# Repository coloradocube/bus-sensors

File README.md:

# Satellite bus sensors

A separate board containing the sensors for the satellite bus. The sensors are telemetry data sources.

## Sensor information

### High-precision temperature sensor (external)

1. Part number: TMP117.
2. Form factor: Breakout.
3. Product page: https://www.sparkfun.com/products/15805
4. Vendor: SparkFun
5. SKU: SEN-15805
6. Board-level connector:
   1. Format: Surface-mount.
   2. Product page: https://www.sparkfun.com/products/14417
   3. Vendor: SparkFun
   4. SKU: PRT-14417
   5. 2D/3D models page: https://www.snapeda.com/parts/PRT-14417/SparkFun%20Electronics/view-part/
   6. KiCAD footprint: https://github.com/KiCad/Connectors_JST.pretty/blob/master/JST_SH_BM04B-SRSS-TB_04x1.00mm_Straight.kicad_mod
7. Operating voltage (typical): 1.8V-5.5V (3.3V).

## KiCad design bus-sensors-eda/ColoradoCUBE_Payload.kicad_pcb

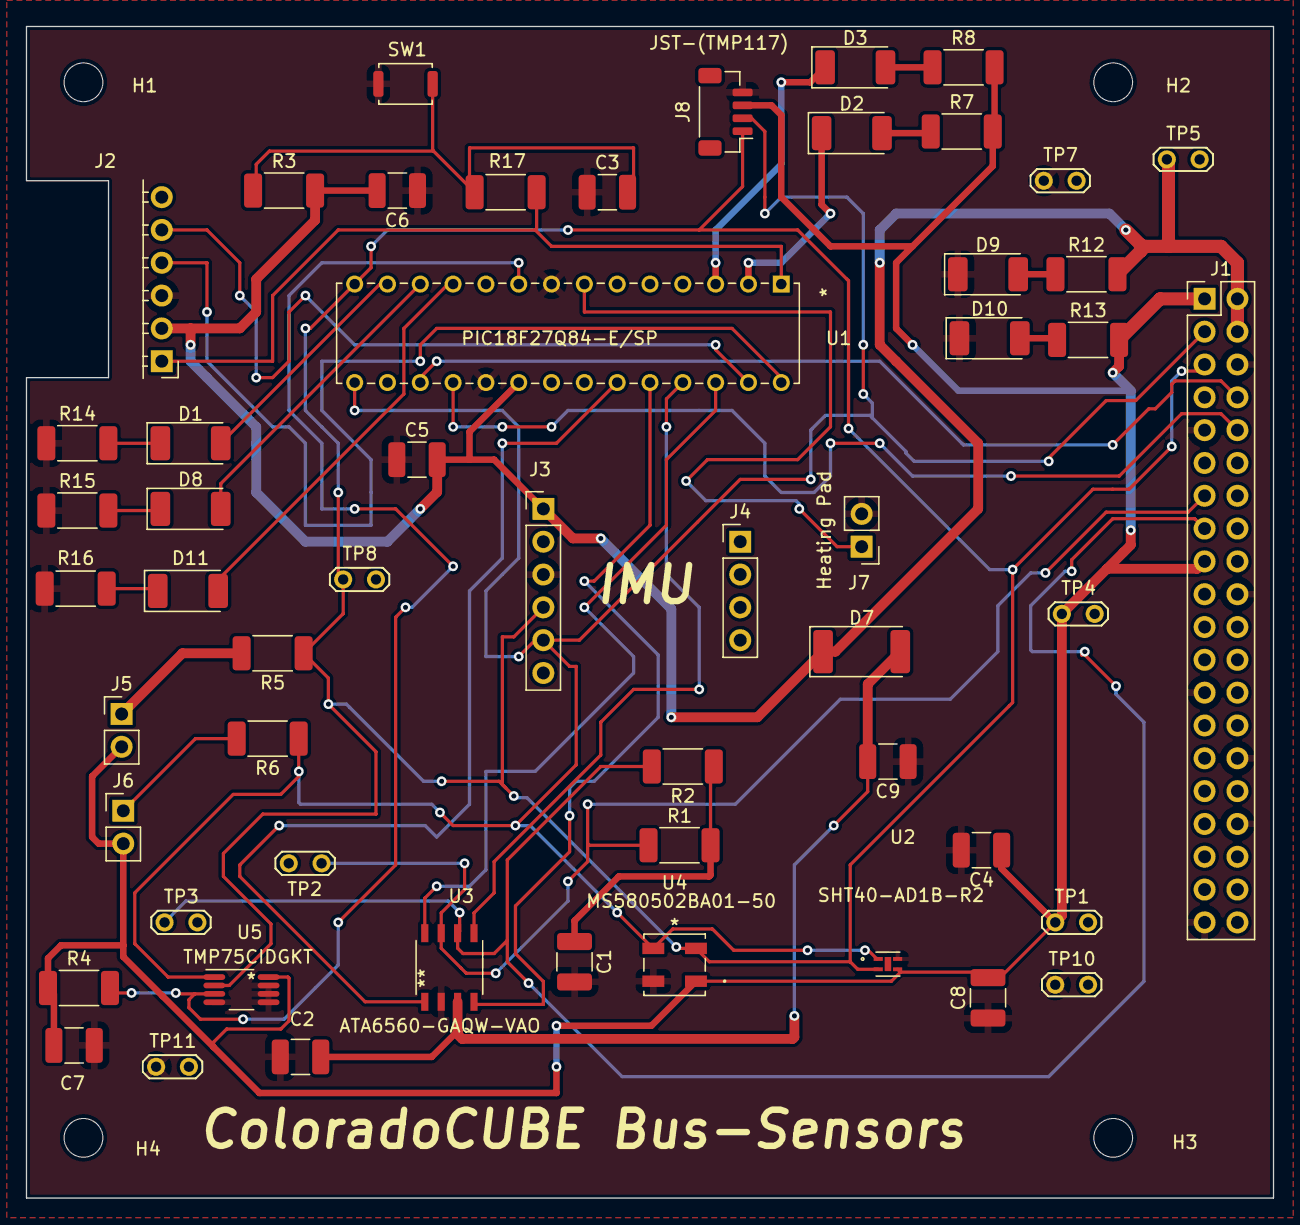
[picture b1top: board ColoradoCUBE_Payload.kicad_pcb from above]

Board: 2 copper layers, 96.5 x 90.7 mm, 58 parts (0 on the bottom side), 35 nets.

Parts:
C1: 4.7nF; C_1210_3225Metric_Pad1.33x2.70mm_HandSolder
C2: 100nF; C_1210_3225Metric_Pad1.33x2.70mm_HandSolder
C3, C4, C5, C6, C7, C8: 0.1uF; C_1210_3225Metric_Pad1.33x2.70mm_HandSolder
C9: 22uF; C_1210_3225Metric_Pad1.33x2.70mm_HandSolder
D1, D8, D11: LED_Filled; LED_2010_5025Metric_Pad1.52x2.65mm_HandSolder
D2, D9, D10: RED; LED_2010_5025Metric_Pad1.52x2.65mm_HandSolder
D3: GREEN; LED_2010_5025Metric_Pad1.52x2.65mm_HandSolder
D7: DIODE; D_2512_6332Metric_Pad1.52x3.35mm_HandSolder
H1, H2, H3, H4: 3mm_Mounting_Hole; MountingHole_3mm
J1: Conn_02x20_Odd_Even; PinHeader_2x20_P2.54mm_Vertical
J2: Conn_01x06; PinHeader_1x06_P2.54mm_Horizontal
J3: Conn_01x06; PinHeader_1x06_P2.54mm_Vertical
J4: Conn_01x04; PinHeader_1x04_P2.54mm_Vertical
J5, J6, J7: Conn_01x02; PinHeader_1x02_P2.54mm_Vertical
J8: Conn_01x04; JST_SH_BM04B-SRSS-TB_1x04-1MP_P1.00mm_Vertical
R1, R2: 60; R_2010_5025Metric_Pad1.40x2.65mm_HandSolder
R3, R4: 10K; R_2010_5025Metric_Pad1.40x2.65mm_HandSolder
R5, R6: 10k; R_2010_5025Metric_Pad1.40x2.65mm_HandSolder
R7, R8: 330; R_2010_5025Metric_Pad1.40x2.65mm_HandSolder
R12: 470; R_2010_5025Metric_Pad1.40x2.65mm_HandSolder
R13: 270; R_2010_5025Metric_Pad1.40x2.65mm_HandSolder
R14, R15, R16: 1k; R_2010_5025Metric_Pad1.40x2.65mm_HandSolder
R17: 100; R_2010_5025Metric_Pad1.40x2.65mm_HandSolder
SW1: SW_SPST; SW_Push_SPST_NO_Alps_SKRK
TP1, TP2, TP3, TP4, TP5, TP7, TP8, TP10, TP11: TestPoint; TestPoint_2Pads_Pitch2.54mm_Drill0.8mm
U1: PIC18F27Q84-E/SP; PIC18F27Q84-E&slash_SP
U2: SHT40-AD1B-R2
U3: ATA6560-GAQW-VAO
U4: MS580502BA01-50
U5: TMP75CIDGKT

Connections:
/+3V3_VDD: C4.1, C7.2, C8.2, J1.1, J1.17, J5.2, J6.2, J8.3, R4.1, R7.2, R8.2, R13.2, TP1.1, TP4.1, U2.3 (VDD), U4.1 (VDD), U5.8 (VS)
/+5V_VDD: C5.2, C6.2, D7.1 (A), J1.2, J1.4, J2.2, J3.1, R3.2, R12.2, TP5.1, U1.20 (VDD)
/ALERT_TEM: R4.2, U1.9 (RA7), U5.3 (ALERT)
/CAN_Transceiver/CANH: J1.13, R1.1, TP2.1, U3.7 (CANH)
/CAN_Transceiver/CANL: J1.15, R2.2, TP3.1, U3.6 (CANL)
/CAN_Transceiver/CAN_RX: U1.24 (RB3), U3.4 (RXD)
/CAN_Transceiver/CAN_TX: U1.23 (RB2), U3.1 (TXD)
/CAN_Transceiver/NSIL: U1.25 (RB4), U3.5 (NSIL)
/CAN_Transceiver/PWR: C2.1, C9.2, D7.2 (K), U3.3 (VCC)
/CAN_Transceiver/STBY: U1.26 (RB5), U3.8 (STBY)
/ICSPC: J2.5, U1.27 (RB6/ICSPCLK)
/ICSPD: J2.4, U1.28 (RB7/ICSPDAT)
/LED_1: D2.1 (K), U1.2 (RA0)
/LED_2: D3.1 (K), U1.3 (RA1)
/MCLR: J2.1, R17.2, U1.1 (*MCLR/VPP/RE3)
/RC0_D11: D11.2 (A), U1.11 (RC0)
/RC1_D12: D8.2 (A), U1.12 (RC1)
/RC2_D13: D1.2 (A), U1.13 (RC2)
/RC6_TX: J1.8, U1.17 (RC6)
/RC7_RX: J1.10, U1.18 (RC7)
/SCL_RC3: J1.5, J3.4, J8.1, R5.1, TP8.1, U1.14 (RC3), U2.2 (SCL), U4.2 (SCL), U5.2 (SCL)
/SDA_RC4: J1.3, J3.5, J8.2, R6.1, U1.15 (RC4), U2.1 (SDA), U4.3 (SDA), U5.1 (SDA)
GND: C1.2, C2.2, C3.1, C4.2, C5.1, C6.1, C7.1, C8.1, C9.1, D9.1 (K), D10.1 (K), J1.6, J1.9, J1.20, J1.25, J1.30, J1.34, J1.39, J2.3, J3.3, J7.2, J8.4, R14.2, R15.2, R16.2, SW1.1 (A), TP7.1, TP10.1, TP11.1, U1.8 (VSS), U1.19 (VSS), U2.4 (VSS), U3.2 (GND), U4.4 (GND), U5.4 (GND), U5.5 (A2), U5.6 (A1), U5.7 (A0)
unnamed: C1.1, R1.2, R2.1
unnamed: C3.2, R3.1, R17.1, SW1.2 (B)
unnamed: D1.1 (K), R14.1
unnamed: D2.2 (A), R7.1
unnamed: D3.2 (A), R8.1
unnamed: D8.1 (K), R15.1
unnamed: D9.2 (A), R12.1
unnamed: D10.2 (A), R13.1
unnamed: D11.1 (K), R16.1
unnamed: J5.1, R5.2
unnamed: J6.1, R6.2
unnamed: J7.1, U1.7 (RA5)

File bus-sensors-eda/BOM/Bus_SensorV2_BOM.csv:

Component Count:,54,,,,,,,,,,
,,,,,,,,,,,
Ref,Qnty,Value,Cmp name,Footprint,Description,JLCPCBPRT#,Digi-Key PRT#,SparkFun,Mouser PRT #,Purchase Link,
,,,,,,,,,,,
"C1, ",1,4.7nF,C,Capacitor_SMD:C_1210_3225Metric_Pad1.33x2.70mm_HandSolder,Unpolarized capacitor,,,,,,
,,,,,,,,,,,
"C2, ",1,100nF,C,Capacitor_SMD:C_1210_3225Metric_Pad1.33x2.70mm_HandSolder,Unpolarized capacitor,,,,,,
,,,,,,,,,,,
"C3, C4, C5, C6, C7, C8, ",6,0.1uF,C,Capacitor_SMD:C_1210_3225Metric_Pad1.33x2.70mm_HandSolder,Unpolarized capacitor,,,,,,
,,,,,,,,,,,
"C9, ",1,22uF,C,Capacitor_SMD:C_1210_3225Metric_Pad1.33x2.70mm_HandSolder,Unpolarized capacitor,,,,,,
,,,,,,,,,,,
"D1, D8, D11, ",3,LED_Filled,LED_Filled,LED_SMD:LED_2010_5025Metric_Pad1.52x2.65mm_HandSolder,"Light emitting diode, filled shape",,,,,,
,,,,,,,,,,,
"D2, D9, D10, ",3,RED,LED_Small_Filled,LED_SMD:LED_2010_5025Metric_Pad1.52x2.65mm_HandSolder,"Light emitting diode, small symbol, filled shape",,,,,,
,,,,,,,,,,,
"D3, ",1,GREEN,LED_Small_Filled,LED_SMD:LED_2010_5025Metric_Pad1.52x2.65mm_HandSolder,"Light emitting diode, small symbol, filled shape",,,,,,
,,,,,,,,,,,
"D7, ",1,DIODE,DIODE,Diode_SMD:D_2512_6332Metric_Pad1.52x3.35mm_HandSolder,"Diode, anode on pin 1, for simulation only!",,,,,,
,,,,,,,,,,,
"J1, ",1,Conn_02x20_Odd_Even,Conn_02x20_Odd_Even,Connector_PinHeader_2.54mm:PinHeader_2x20_P2.54mm_Vertical,"Generic connector, double row, 02x20, odd/even pin numbering scheme (row 1 odd numbers, row 2 even numbers), script generated (kicad-library-utils/schlib/autogen/connector/)",C124383,,,,,
,,,,,,,,,,,
"J2, ",1,Conn_01x06,Conn_01x06,Connector_PinHeader_2.54mm:PinHeader_1x06_P2.54mm_Horizontal,"Generic connector, single row, 01x06, script generated (kicad-library-utils/schlib/autogen/connector/)",C56816,,,,,
,,,,,,,,,,,
"J3, ",1,Conn_01x06,Conn_01x06,Connector_PinHeader_2.54mm:PinHeader_1x06_P2.54mm_Vertical,"Generic connector, single row, 01x06, script generated (kicad-library-utils/schlib/autogen/connector/)",C37208,,,,,
,,,,,,,,,,,
"J4, ",1,Conn_01x04,Conn_01x04,Connector_PinHeader_2.54mm:PinHeader_1x04_P2.54mm_Vertical,"Generic connector, single row, 01x04, script generated (kicad-library-utils/schlib/autogen/connector/)",C492403,,,,,
,,,,,,,,,,,
"J5, J6, J7, ",3,Conn_01x02,Conn_01x02,Connector_PinHeader_2.54mm:PinHeader_1x02_P2.54mm_Vertical,"Generic connector, single row, 01x02, script generated (kicad-library-utils/schlib/autogen/connector/)",C358684,,,,,
,,,,,,,,,,,
"J8, ",1,Conn_01x04,Conn_01x04,Connector_JST:JST_SH_BM04B-SRSS-TB_1x04-1MP_P1.00mm_Vertical,"Generic connector, single row, 01x04, script generated (kicad-library-utils/schlib/autogen/connector/)",C492403,,,,,
,,,,,,,,,,,
"R1, R2, ",2,60,R,Resistor_SMD:R_2010_5025Metric_Pad1.40x2.65mm_HandSolder,Resistor,,,,,,
,,,,,,,,,,,
"R3, R4, ",2,10K,R,Resistor_SMD:R_2010_5025Metric_Pad1.40x2.65mm_HandSolder,Resistor,,,,,,
,,,,,,,,,,,
"R5, R6, ",2,10k,R,Resistor_SMD:R_2010_5025Metric_Pad1.40x2.65mm_HandSolder,Resistor,,,,,,
,,,,,,,,,,,
"R7, R8, ",2,330,R,Resistor_SMD:R_2010_5025Metric_Pad1.40x2.65mm_HandSolder,Resistor,,,,,,
,,,,,,,,,,,
"R12, ",1,470,R,Resistor_SMD:R_2010_5025Metric_Pad1.40x2.65mm_HandSolder,Resistor,,,,,,
,,,,,,,,,,,
"R13, ",1,270,R,Resistor_SMD:R_2010_5025Metric_Pad1.40x2.65mm_HandSolder,Resistor,,,,,,
,,,,,,,,,,,
"R14, R15, R16, ",3,1k,R,Resistor_SMD:R_2010_5025Metric_Pad1.40x2.65mm_HandSolder,Resistor,,,,,,
,,,,,,,,,,,
"R17, ",1,100,R,Resistor_SMD:R_2010_5025Metric_Pad1.40x2.65mm_HandSolder,Resistor,,,,,,
,,,,,,,,,,,
"SW1, ",1,SW_SPST,SW_SPST,Button_Switch_SMD:SW_Push_SPST_NO_Alps_SKRK,Single Pole Single Throw (SPST) switch,C426027,,,,,
,,,,,,,,,,,
"TP1, TP2, TP3, TP4, TP5, TP7, TP8, TP10, TP11, ",9,TestPoint,TestPoint,TestPoint:TestPoint_2Pads_Pitch2.54mm_Drill0.8mm,test point,5003,,,,,
,,,,,,,,,,,
"U1, ",1,PIC18F27Q84-E/SP,PIC18F27Q84-E{slash}SP,footprintsSP:PIC18F27Q84-E&slash_SP,,,,,,,
,,,,,,,,,,,
"U2, ",1,SHT40-AD1B-R2,SHT40-AD1B-R2,tem_sensor:SHT40-AD1B-R2,,  ,1649-SHT40I-AD1B-R2TR-ND,,,https://www.digikey.com/en/products/detail/sensirion-ag/SHT4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,
,,,,,,,,,,,
"U3, ",1,ATA6560-GAQW-VAO,ATA6560-GAQW-VAO,CAN_footprint:ATA6560-GAQW-VAO,,,,,,,
,,,,,,,,,,,
"U4, ",1,MS580502BA01-50,MS580502BA01-50,MS5805:MS580502BA01-50,,,,,824-MS580502BA01-50,https://www.mouser.com/ProductDetail/Measurement-Specialties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,
,,,,,,,,,,,
"U5, ",1,TMP75CIDGKT,TMP75CIDGKT,TEM_S:TMP75CIDGKT,,,,PRT - 14417,,https://www.sparkfun.com/products/14417,
,,,,,,,,,,,
Other Sensor,50251,,TMP 117 (Qwiic),uses PRT U5 to connect,,,,SEN-15805 RHOS,,https://www.sparkfun.com/products/15805,

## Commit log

2022-04-21 ignore zip archives
2022-04-21 first separate sensors commit
2022-04-23 added qwiic connector footprint file
2022-04-25 Bus_Sensors
    Latest Update
2022-04-25 added bom dir to eda
2022-04-25 Bus-Sensor-BOM-V2
2022-04-25 moving files under eda dir
2022-04-25 courtyards and silkscreens correction
2022-04-28 Removed errors after updating PCB from schematic
2022-05-04 minor bom touchup
2022-05-04 ignore excel and zip

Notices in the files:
parts and their libraries:
Copyright 2021 Accelerated Designs. All rights reserved.
